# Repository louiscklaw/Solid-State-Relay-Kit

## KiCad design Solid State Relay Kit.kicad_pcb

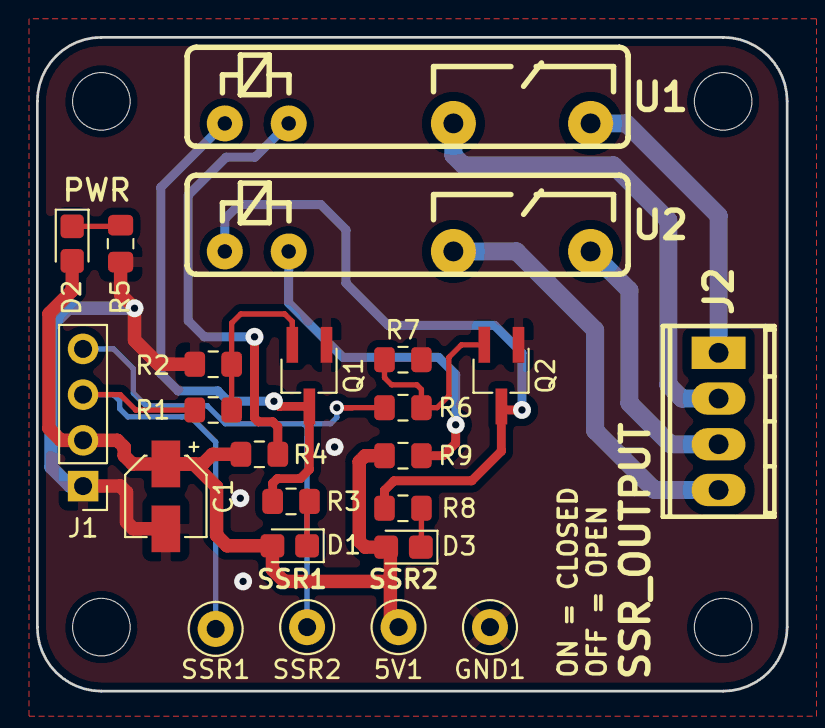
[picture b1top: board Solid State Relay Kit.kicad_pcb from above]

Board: 2 copper layers, 41.7 x 36.3 mm, 23 parts (0 on the bottom side), 17 nets.

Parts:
5V1: TestPoint; TestPoint_Loop_D1.80mm_Drill1.0mm_Beaded
C1: 105; CP_Elec_4x3
D1, D2, D3: LED; LED_0805_2012Metric_Castellated
GND1: TestPoint; TestPoint_Loop_D1.80mm_Drill1.0mm_Beaded
J1: Conn_01x03; PinHeader_1x04_P2.54mm_Vertical
J2: SSR_OUTPUT; mpt_0,5%2f4-2,54
Q1, Q2: 2N3904; TSOT-23_HandSoldering
R1, R3, R6, R8: 331; R_0805_2012Metric_Pad1.15x1.40mm_HandSolder
R2, R7: 103; R_0805_2012Metric_Pad1.15x1.40mm_HandSolder
R4, R9: 680; R_0805_2012Metric_Pad1.15x1.40mm_HandSolder
R5: 104; R_0805_2012Metric_Pad1.15x1.40mm_HandSolder
SSR1, SSR2: TestPoint; TestPoint_Loop_D1.80mm_Drill1.0mm_Beaded
U1, U2: OMRON G3MB-202P; OMRON-G3MB-202P

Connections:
+5V: 5V1.1, C1.1, D1.2, D2.2, D3.2, J1.2, R4.1, R9.1
/SSR1_IN1: Q1.3, R3.2, U1.4
/SSR1_IN2: R4.2, U1.3
/SSR1_OUT1: J2.2, U1.2
/SSR1_OUT2: J2.1, U1.1
/SSR2_IN1: Q2.3, R8.2, U2.4
/SSR2_IN2: R9.2, U2.3
/SSR2_OUT1: J2.4, U2.2
/SSR2_OUT2: J2.3, U2.1
/SSR_CONTROL1: J1.3, R1.2, SSR1.1
/SSR_CONTROL2: J1.4, R6.2, SSR2.1
GND: C1.2, GND1.1, J1.1, Q1.1, Q2.1, R2.2, R5.2, R7.2
unnamed: D1.1, R3.1
unnamed: D2.1, R5.1
unnamed: D3.1, R8.1
unnamed: Q1.2, R1.1, R2.1
unnamed: Q2.2, R6.1, R7.1

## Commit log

2018-10-07 update,
2018-10-10 update comment,
2018-10-11 start panelizing,
2018-10-11 simplify tracks,.
2020-05-07 ci: init travis token,
2020-05-07 ci: init travis build config,
